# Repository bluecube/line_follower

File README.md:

Line follower v2
================

This is a robot I made to tinker with and to compete in the [Robotic Day](https://roboticday.org/) competition. (Actually the original goal was Robotic Day 2016, but stuff got delayed :) )

The design is an attempt to make a line follower with minimum effort on the hardware side and maximum versatility on the software side.

The robot body consists of a 8cm x 10cm double sided PCB, two geared N20 DC encoder motors with Pololu wheels and magnetic encoders and a few 3D printed bits.
The most important electronic components are ESP32 development board for computing power and line sensor inspired by [Ondřej Staněk's PocketBot](http://www.ostan.cz/pocketBot/), as a bonus the robot also carries an IR range sensor and MPU 6050 breakout board (accelerometer and gyro).

This repository should contain everything necessary to build and run the robot in the competition.
Let me know if you decide to build it!

This is a v2, you can also check out the [v1](https://github.com/bluecube/line_follower/tree/v1/).

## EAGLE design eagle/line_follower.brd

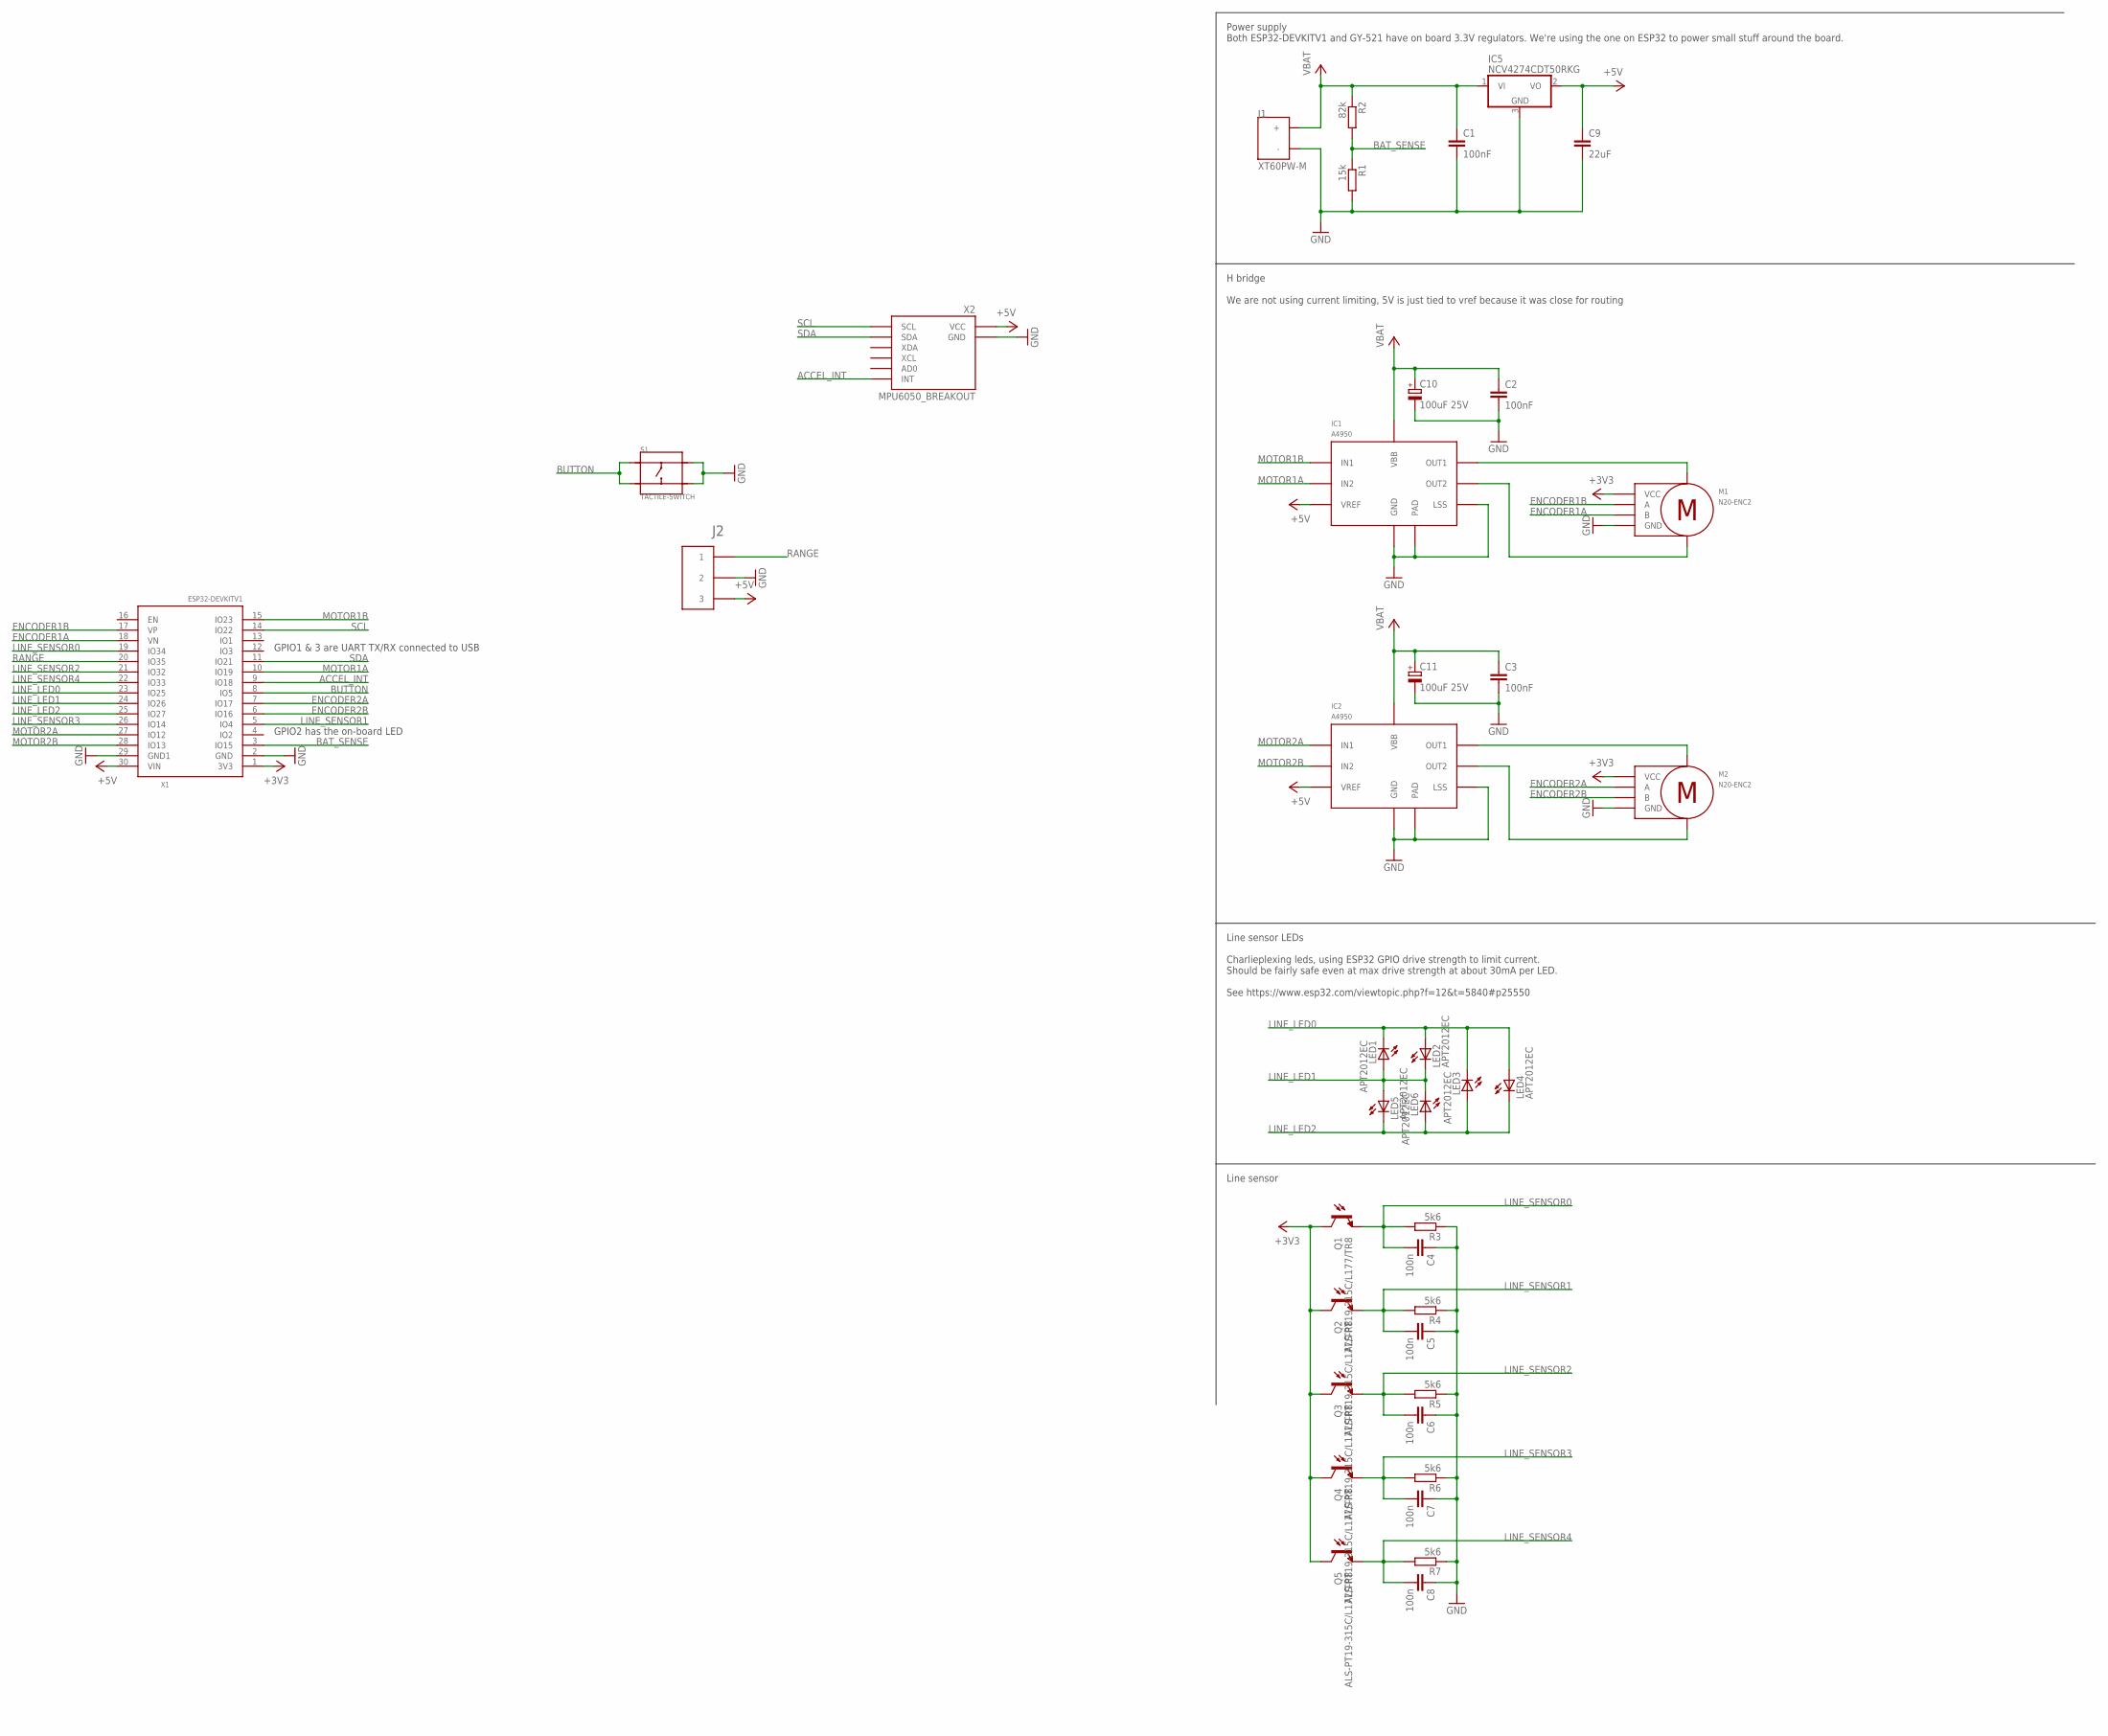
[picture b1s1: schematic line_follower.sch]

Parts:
C1, C2, C3: 100nF; C0805
C4, C5, C6, C7, C8: 100n; C0805
C9: 22uF; C0805
C10, C11: 100uF 25V; UD-6,3X5,8_NICHICON
IC1, IC2: A4950; SOIC8_PAD
IC5: NCV4274CDT50RKG; TO252
J1: XT60PW-M
J2: 2.54MM_HEADER_3X1
LED1, LED2, LED3, LED4, LED5, LED6: APT2012EC; CHIP-LED0805
M1, M2: N20-ENC2; 2.54MM_HEADER_6X1
Q1, Q2, Q3, Q4, Q5: ALS-PT19-315C/L177/TR8; PHOTOTRANSISTOR-1.7MM
R1: 15k; R0805
R2: 82k; R0805
R3, R4, R5, R6, R7: 5k6; R0805
S1: TACTILE-SWITCH; SW4-SMD-4.5MM
X1: ESP32DEVKITV1; ESP32-DEVKITV1
X2: MPU6050_BREAKOUT

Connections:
+3V3: M1.P$5 (VCC), M2.P$5 (VCC), Q1.C, Q2.C, Q3.C, Q4.C, Q5.C, X1.1 (3V3)
+5V: C9.1, IC1.4 (VREF), IC2.4 (VREF), IC5.2 (VO), J2.P$3 (3), X1.30 (VIN), X2.P$1 (VCC)
ACCEL_INT: X1.9 (IO18), X2.P$8 (INT)
BAT_SENSE: R1.1, R2.2, X1.3 (IO15)
BUTTON: S1.P$1 (A0), S1.P$3 (B0), X1.8 (IO5)
ENCODER1A: M1.P$4 (B), X1.18 (VN)
ENCODER1B: M1.P$3 (A), X1.17 (VP)
ENCODER2A: M2.P$3 (A), X1.7 (IO17)
ENCODER2B: M2.P$4 (B), X1.6 (IO16)
GND: C1.2, C2.2, C3.2, C4.1, C5.1, C6.1, C7.1, C8.1, C9.2, C10.-, C11.-, IC1.1 (GND), IC1.7 (LSS), IC1.PAD, IC2.1 (GND), IC2.7 (LSS), IC2.PAD, IC5.3 (GND), J1.NEG (-), J2.P$2 (2), M1.P$2 (GND), M2.P$2 (GND), R1.2, R3.1, R4.1, R5.1, R6.1, R7.1, S1.P$2 (A1), S1.P$4 (B1), X1.2 (GND), X1.29 (GND1), X2.P$2 (GND)
LINE_LED0: LED1.C, LED2.A, LED3.C, LED4.A, X1.23 (IO25)
LINE_LED1: LED1.A, LED2.C, LED5.A, LED6.C, X1.24 (IO26)
LINE_LED2: LED3.A, LED4.C, LED5.C, LED6.A, X1.25 (IO27)
LINE_SENSOR0: C4.2, Q1.E, R3.2, X1.19 (IO34)
LINE_SENSOR1: C5.2, Q2.E, R4.2, X1.5 (IO4)
LINE_SENSOR2: C6.2, Q3.E, R5.2, X1.21 (IO32)
LINE_SENSOR3: C7.2, Q4.E, R6.2, X1.26 (IO14)
LINE_SENSOR4: C8.2, Q5.E, R7.2, X1.22 (IO33)
MOTOR1A: IC1.2 (IN2), X1.10 (IO19)
MOTOR1B: IC1.3 (IN1), X1.15 (IO23)
MOTOR2A: IC2.3 (IN1), X1.27 (IO12)
MOTOR2B: IC2.2 (IN2), X1.28 (IO13)
unnamed: IC2.6 (OUT1), M2.P$1 (M+)
unnamed: IC1.6 (OUT1), M1.P$1 (M+)
unnamed: IC1.8 (OUT2), M1.P$6 (M-)
unnamed: IC2.8 (OUT2), M2.P$6 (M-)
RANGE: J2.P$1 (1), X1.20 (IO35)
SCL: X1.14 (IO22), X2.P$3 (SCL)
SDA: X1.11 (IO21), X2.P$4 (SDA)
VBAT: C1.1, C2.1, C3.1, C10.+, C11.+, IC1.5 (VBB), IC2.5 (VBB), IC5.1 (VI), J1.POS (+), R2.1

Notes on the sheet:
Line sensor
H bridge We are not using current limiting, 5V is just tied to vref because it was close for routing
Power supply Both ESP32-DEVKITV1 and GY-521 have on board 3.3V regulators. We're using the one on ESP32 to power small stuff around the board.
Line sensor LEDs Charlieplexing leds, using ESP32 GPIO drive strength to limit current. Should be fairly safe even at max drive strength at about 30mA per LED. See https://www.esp32.com/viewtopic.php?f=12&t=5840#p25550
GPIO1 & 3 are UART TX/RX connected to USB
GPIO2 has the on-board LED

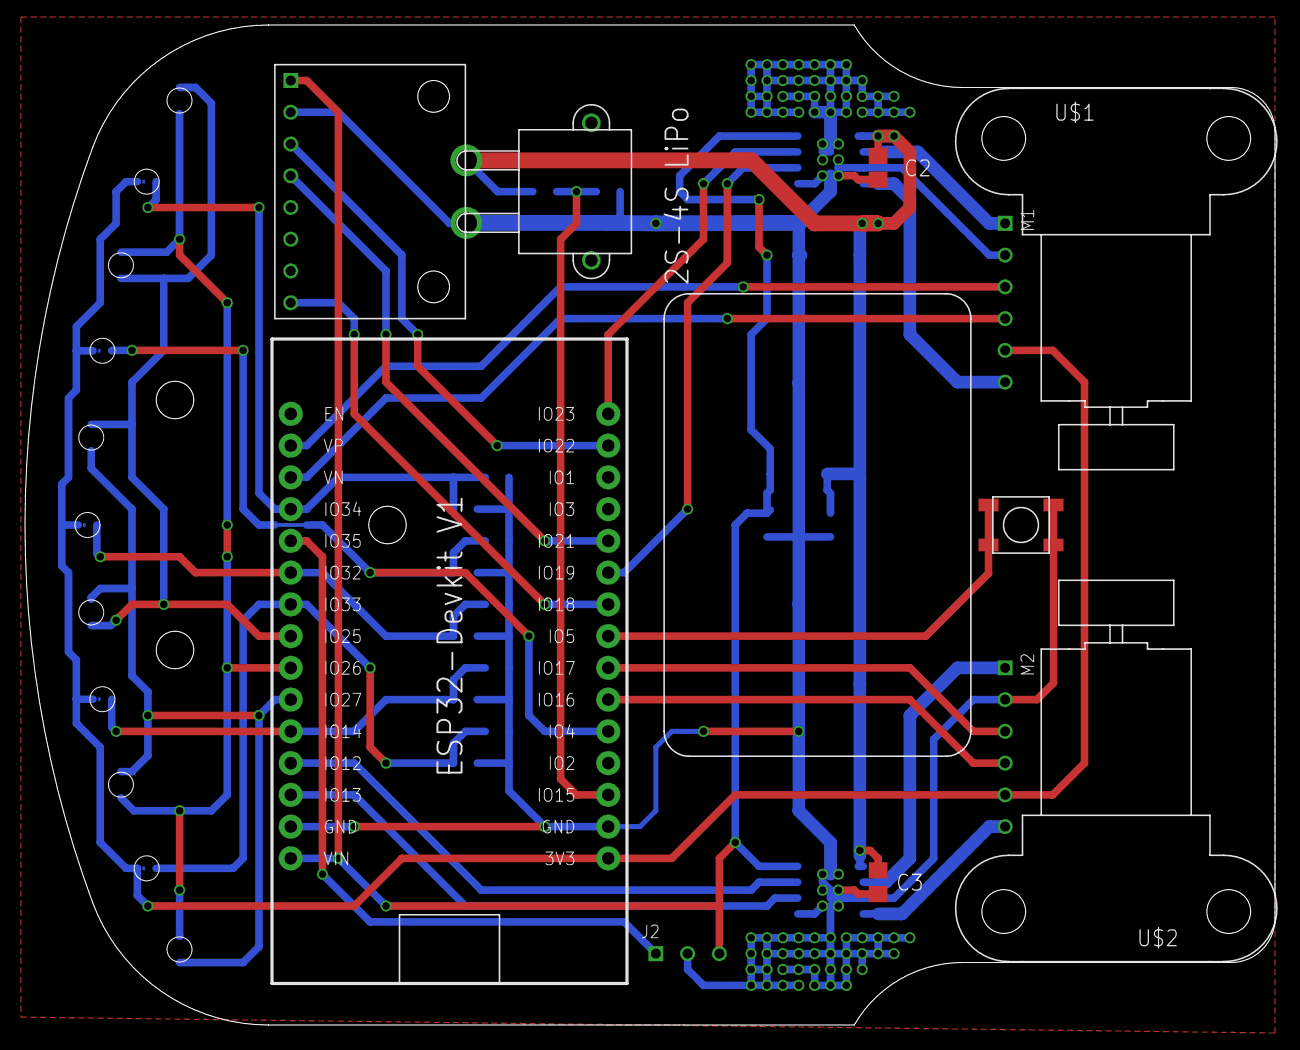
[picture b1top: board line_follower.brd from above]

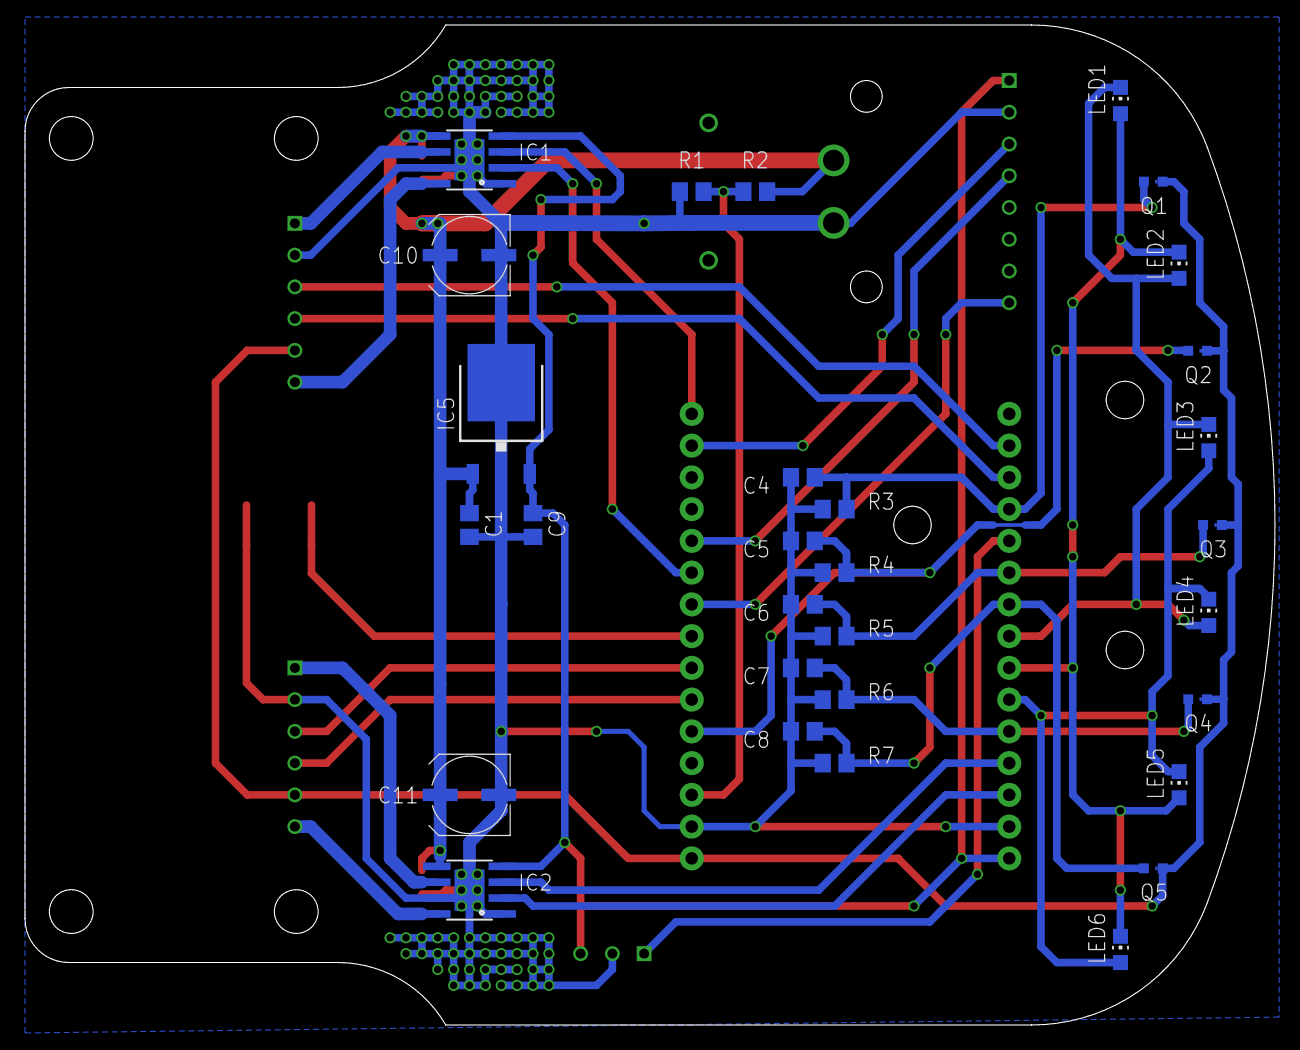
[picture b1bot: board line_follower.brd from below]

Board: 2 copper layers, 100.0 x 80.0 mm, 41 parts (30 on the bottom side), 30 nets.

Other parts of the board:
U$1, U$2: N20-ENC-NOPIN

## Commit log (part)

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2016-04-03 Initial commit.
    3D sketch in solidworks and almost finished board.
2016-04-16 Fixes before sending the board for fab.
2016-05-12 Got rid of old versions of model.
2016-05-28 Testing arena design.
2016-05-29 Added missing connections to the board.
2016-06-27 Updated the testing map to 1x1.5m format.
2016-06-29 Updated testing map
2016-07-03 One more change of the testing map.
    I should really be doing more useful stuff :-)
2016-10-12 Blink zinc example that compiles
2016-10-12 Very rough (non compilable by far) idea of top level code separation
2017-02-13 More realistic wheel shape
2017-02-13 3D printable distance sensor bracket, front ball and motor brackets.
2017-02-13 Removed unused solidworks parts
2017-05-28 Working blink example
2018-12-16 Cleaned up old attempts
2019-01-06 Crosstool configuration for building the toolchain.
2019-01-06 Cleaning up the remaining pieces of rust coniguration.
2019-04-14 Starting with C++ project
2019-04-15 Larson scanner hello world with arduino.
2019-04-27 Settled on using Arduino with platformio.
2019-04-28 Playing with LEDs
2019-04-28 Added comment.
2019-04-28 Very simple reading of analog values.
2019-05-18 Carrying case first draft
2019-05-19 Short introduction text for Robotic Day 2019
2019-05-19 Robotic day photos.
2019-05-19 Fixed values of line sensor divider resistors.
2019-05-19 Started a list of hardware bugs.
2019-05-19 Some work done on the carrying box.
2019-05-19 Small change in robotic day introduction
2019-05-19 Readme improvements.
2019-05-20 Added a github link to short introduction file
2019-05-20 Create LICENSE
2019-05-21 Added jupyter notebook containing experiments with line detection cross-corelation kernels
2019-05-21 Line sensor reacts now.
2019-05-21 One more (minor) hardware bug.
2019-05-21 Prepared testing map for printing
2019-05-26 Carrying box ready for printing.
2019-05-26 Cleaning up line sensor code, using at least a few parallel ADC reads.
2019-05-27 Fixing uninitialized ADC instance after move to singleton.
2019-05-28 Line detection working.
2019-05-29 Simplified line detector.
2019-05-29 Renamed LfHal to RobotHal
2019-05-30 Debounced button input.
2019-05-31 Cleaning up Hal, simplified the replacability.
2019-06-01 Fixed changing motor directions (analogWrite and digitealWrite don't mix)
2019-06-01 State machine with basic line following code
2019-06-01 Added bootup state.
2019-06-01 Setting loop period
2019-06-01 Somehow working line following
2019-06-01 Fixing missing enum members in switch
2019-06-01 Rudimentary battery voltage monitoring
2019-06-01 Still fiddling with parameters
2019-06-02 Smoother line finding.
2020-04-25 Schematic for V2 mostly complete, time to work on the board.
2020-04-26 Removed obsolete solidworks models
2020-04-26 Updated gitignore
2020-04-26 You'll have to google for the datasheets yourself.
2020-04-26 Rough layout of the new board
2020-04-29 Modelled a bunch of new parts for the robot
2020-04-29 Decided to not use the encoder board on the motors, schematic tweaks and start of layout
2020-05-19 Motor encoder boards are back, more layout work
2020-05-20 Another quarter-afternoon of layout
2020-05-22 Everything is connected on the board, but more work remains
2020-05-22 Layout complete, now a day or two for it to sink in and find more errors.
2020-06-04 started working on kicad version of the board
2020-07-01 Board: Almost complete schematic, rough layout of pcb
2020-07-01 WIP mechanical design in F360
2020-07-23 Getting there with the PCB design.
2020-07-24 Updated sensor components position export
2020-08-02 Board done except for the motor mounts
2020-08-02 Small PCB tweaks
2020-08-02 Placed motor mounting holes and silkscreen outlines.
    Board done for now.
2020-08-09 Untangled routing at the front of the robot a bit, moved battery location
2020-08-10 board: A bit more tweaking
2020-08-10 board: Moving silkscreen labels
2020-08-13 board: Manually fixed the outline to make step exporter happy
2020-08-15 Ignoring kicad autosave files.
2020-08-15 mechanical: WIP 3d printed parts and robot layout
    Front top and bottom pieces are ready, motor mounts and deck are missing
2020-08-26 board: Added model for microswitch
2020-08-26 board: Some silkscreen change ...
2020-08-26 schematic: Fixing DRC warnings
2020-08-26 schematic: Removed comment
2020-08-26 board: Small tweaks + updating to match previous changes.
2020-08-26 board: Gerber files, sent for manufacture
2020-10-02 CAD model ready for 3D printing
2020-10-02 Added Step export of the CAD model
2020-10-06 mechanical: Updated based experimental prints.
2020-10-14 schematic: Modified power supply LDO because of availability at Mouser.
2020-10-14 mechanical: More updates, refreshed exports
2020-10-15 mechanical: Cleanup + added readme
2020-11-08 Set theme jekyll-theme-cayman
2020-11-12 Exporter script for the Fusion360 design
2020-11-12 schematic: Changed the 5V regulator again
    the previous one had wrong pinout
2020-11-12 mechanical: Printability improvements and smaller tweaks
2020-11-13 Renamed kicad exports directory
2020-12-06 Updated platformio to work with ESP32.
2020-12-06 Removed Arduino calls from code except HAL
2020-12-06 Silencing compiler warnings
2020-12-07 RobotHal: Got rid of Arduino remnants
2020-12-07 RobotHal: New pin assignments
2020-12-07 RobotHal: Singleton stuff
2020-12-07 Formating
2020-12-08 Using C++17
2020-12-08 Blinking LEDs through RobotHal
2020-12-10 Removed the obsolete eagle project
2020-12-10 Removed obsolete solidworks designs
2020-12-10 Updated README to reflect the branch renaming
2020-12-10 Fixed image path in readme
2020-12-10 Line sensor buffer definitions.
2020-12-12 Naming convention
2020-12-12 Got rid of time types for now (will be replaced by std::chrono later)
2020-12-12 WIP line sensor reading
2020-12-12 Line sensor kind of working
2020-12-20 Reading motor encoders
2020-12-20 Printf!
2020-12-22 Moved RobotHal to a separate directory
2020-12-22 Coding style change for encoder configuration
2020-12-23 idf_util needed to be moved as well
2020-12-23 Added Vector3D class
2020-12-25 Initial non-working IMU code
2020-12-26 Refactored Line sensor to a separate class under HAL
2020-12-26 IMU HAL component uses static methods rather than HAL reference.
2020-12-26 More reasonable naming scheme for HAL components
2020-12-26 Refactored motor control to separate HAL component
2020-12-26 Utility for checking ESP-IDF error codes
2020-12-26 Debug print tweaks
2020-12-27 HAL: Reading battery voltage
2020-12-27 Removed commented block of old code from main
2020-12-27 HAL: Line sensor LED pins should start as disabled
2020-12-27 HAL: Setting motor PWM
2020-12-27 HAL: Fixing I2C register reading code
2020-12-27 HAL: One more printf during init
2020-12-27 HAL/Mpu6050: Checking connection, attempting to wake from sleep mode
    Connection works, but accelerometer and gyro still read as zeros
2020-12-31 Removed old documentation related to v1
2020-12-31 Moved the line sensor experiments to jupyter directory
2021-01-03 Schematic of the planned balancing algorithm.
2021-01-08 HAL: Motor beeping
2021-02-07 Ignoring jupyter checkpoints
2021-02-07 HAL: Compilation fix for latest ESP-IDF
2021-02-07 HAL: Number of line sensor LEDS must be public
2021-02-07 Preparing PID controller helper for units
2021-02-07 Ignoring Fusion360 plugin junk
2023-01-17 Renamed deprecated config from platformio.ini
2023-02-18 Untested ADC library update.
2023-03-01 Partially converted motor module of HAL to use the new libraries
2023-03-01 Removed motor beeping functionality
2023-03-03 Finalized HAL for motors
2023-03-03 Tweaking shortcuts in makefile
2023-03-05 Ignore warnings from missing field initializers
2023-03-05 Selectable serial port in Makefile
2023-03-05 C++ wrapper for ESP32 high resolution timer
2023-03-05 Using ESP_ERROR_CHECK instead of HAL_CHECK
2023-03-06 Cleaned up includes
2023-03-29 Renamed EspTimer header file, added Clock to Hal
2023-03-29 Removed old button event enum from Hal
2023-03-29 Added Hal sub-component types to typedef, to allow accessing compile time constants
2023-03-29 Fixed a typo
2023-04-10 Renaming Pid to PidController.
2023-04-10 Removed parameters already defined elsewhere
2023-04-10 Remove obsolete commented code from main
2023-04-10 hal: Refactored to a PIO library
2023-04-10 Old state machine almost removed
    We keep the files around to rescue some of the line following code
2023-04-10 Removing old code
2023-04-10 Moved most of functionality to a library
    for easier unit testing
2023-04-18 Unit tesing for the C++ code
2023-04-18 Encoder observer Kalman filter
    Seems to work, but not so great performance yet
2023-04-27 Don't optimize tests at all
2023-04-28 Removed unused code
2023-04-29 Borrowed CircularBuffer from bluecube/tablog
2023-05-04 New version of encoder observer
    uses line fitting of velocitites instead of Kalman filter, adaptive window size.
2023-05-11 Texts for Robotic Day 2023
2023-05-27 HAL abstraction for running periodic tasks
2023-05-27 Initial version of motor velocity controller
2023-05-27 Tweaks in encoder observer
2023-05-28 Create instructions.md
    First try to collect notes about building the robot.
2023-06-12 Measured rangefinder distances for calibration, not finished yet
2023-06-15 Skeleton of rangefinder HAL API.
2023-06-18 Added accessing const data to periodic task
2023-06-18 Reading out current velocity from motor velocity controler
2023-06-27 Changed motors to ones with 1:30 gear ratio
2026-04-23 Setting up LSP in helix
2026-04-23 Starting rust rewrite, Motors work.
2026-04-24 Button handling
2026-04-27 Line sensor LED control
2026-04-27 Updated CLAUDE.md
2026-04-28 Line sensor ADC reading
2026-05-01 Simplified line sensor HAL code
2026-05-01 HAL: Formating button code
2026-05-01 Ranged integers in LineSensor API
2026-05-04 Refactoed Rust rewrite to better separate HAL
2026-05-04 Line detection algorithm
2026-05-04 Moved C++ version into `old-c++-firmware`
2026-05-04 Fixed comments about ADC inversion
2026-05-04 CLAUDE.md tweak
2026-05-04 Reading the battery voltage and WIP reading the distance sensor
2026-05-05 Distance sensor calibration + updated calibration binaries
2026-05-07 Onboard LED
2026-05-08 Added a constant for rough maximum motor speed.
2026-05-09 Mysterious style tweak to line detection
2026-05-11 Velocity controller with preliminary PID tuning
2026-05-11 CLAUDE.md update
2026-05-16 Ignoring pycache
    That should never have been commited..
2026-05-24 Comment changes
2026-05-24 Moving to Embassy for async tasks
2026-05-24 Minor refactoring of set_led
2026-05-24 Updated dependencies
2026-05-25 Moved velocity controller to use embassy_time units instead of raw microseconds
2026-05-27 Making button code async
2026-05-27 Fixing a line sensor bug
    This likely happened when an update of esp-hal fixed the inversion bug
2026-05-27 Async line sensor readout
2026-06-01 Listing all that is wrong with the design and needs to be worked around
2026-06-01 Python client for bluetooth logs
2026-06-01 Removed arrayvec dependency, using heapless::Vec instead
2026-06-05 New HAL tester binary, removed obsolete motor_test.
2026-06-05 Fixing button EMI issues in software only...
2026-06-05 Line detection now exports the PositionT type to communicate the detection value scale.
2026-06-05 Improved HAL test
2026-06-06 Decreased line detection sensitivity, updated tests
2026-06-06 METERS_PER_TICK changed from f64 to f32
2026-06-08 Line following, almost working
2026-06-09 Faster line sensor reading
2026-06-09 Constants describing the hardware in lf-hal-types
2026-06-09 Mandelbrot set benchmark
2026-06-09 Got rid of the old firmware
2026-06-10 Moving line detection and velocity controlller to use `fixed`
2026-06-10 Making clippy happy
2026-06-11 Playing with line following code
2026-06-13 Refactored HAL to have battery and range in separate structs
2026-06-13 Restructured main to use fixed 100Hz update rate, button checking in parallel withh line following
